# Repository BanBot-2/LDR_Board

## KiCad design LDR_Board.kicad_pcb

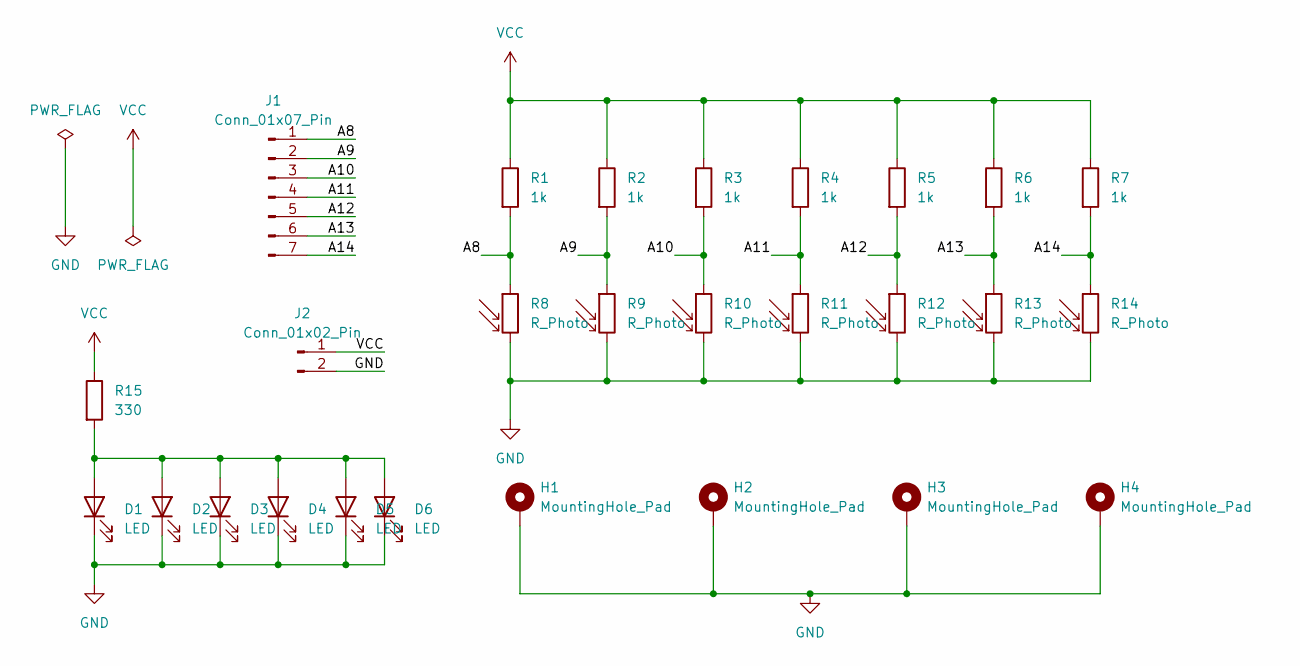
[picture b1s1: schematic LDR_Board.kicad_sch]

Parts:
D1, D2, D3, D4, D5, D6: LED; LED_D5.0mm
H1, H2, H3, H4: MountingHole_Pad; MountingHole_3.2mm_M3_Pad
J1: Conn_01x07_Pin; PinHeader_1x07_P2.54mm_Vertical
J2: Conn_01x02_Pin; PinHeader_1x02_P2.54mm_Vertical
R1, R2, R3, R4, R5, R6, R7: 1k; R_Axial_DIN0207_L6.3mm_D2.5mm_P10.16mm_Horizontal
R8, R9, R10, R11, R12, R13, R14: R_Photo; R_LDR_5.0x4.1mm_P3mm_Vertical
R15: 330; R_Axial_DIN0207_L6.3mm_D2.5mm_P10.16mm_Horizontal

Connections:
/A8: J1.1, R1.2, R8.1
/A9: J1.2, R2.2, R9.1
/A10: J1.3, R3.2, R10.1
/A11: J1.4, R4.2, R11.1
/A12: J1.5, R5.2, R12.1
/A13: J1.6, R6.2, R13.1
/A14: J1.7, R7.2, R14.1
GND: D1.1 (K), D2.1 (K), D3.1 (K), D4.1 (K), D5.1 (K), D6.1 (K), H1.1, H2.1, H3.1, H4.1, J2.2, R8.2, R9.2, R10.2, R11.2, R12.2, R13.2, R14.2
unnamed: D1.2 (A), D2.2 (A), D3.2 (A), D4.2 (A), D5.2 (A), D6.2 (A), R15.2
VCC: J2.1, R1.1, R2.1, R3.1, R4.1, R5.1, R6.1, R7.1, R15.1

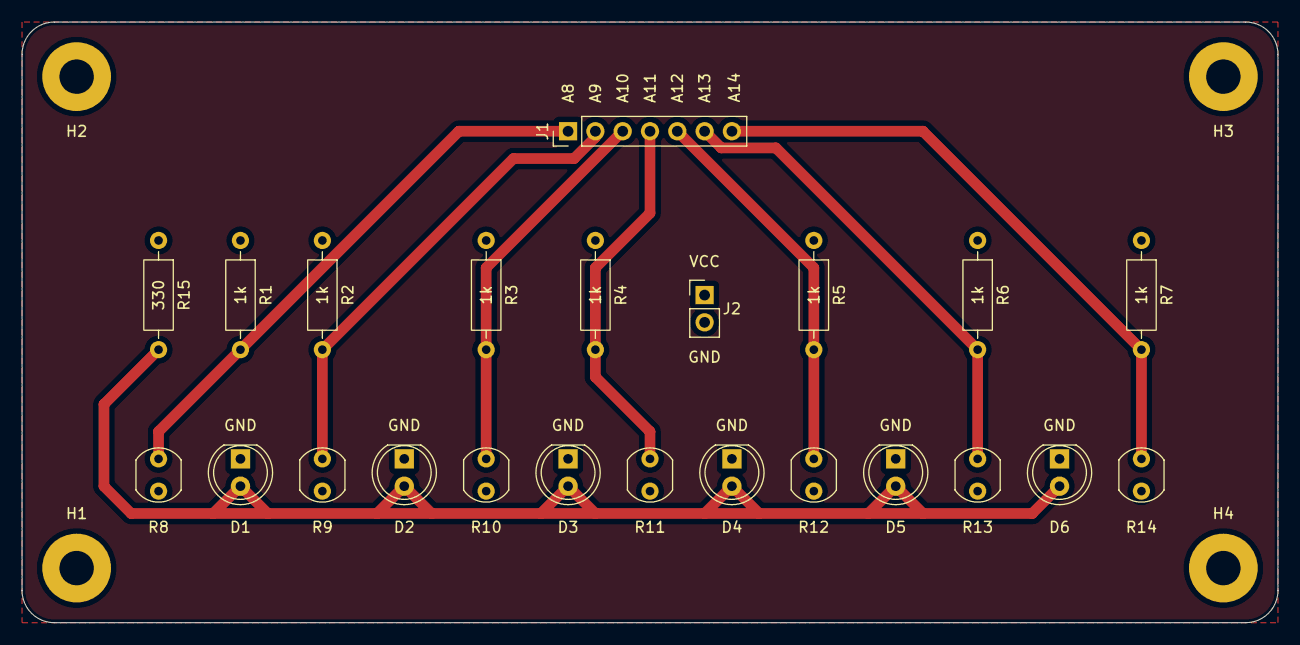
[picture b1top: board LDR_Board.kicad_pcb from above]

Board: 2 copper layers, 116.8 x 55.9 mm, 27 parts (0 on the bottom side), 10 nets.

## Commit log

2026-01-31 Arranged components
    Untangled all the components on the PCB layout and prepared them for running traces. No actual wiring has been done yet.
2026-02-01 Routed traces and added silkscreen
    Still need to export for manufacturing, but initial design is complete.
2026-02-01 Added additional silkscreen
2026-02-02 Exported for manufacturing and submitted
